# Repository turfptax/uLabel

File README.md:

# uLabel
Machine Learning Label System for regression finger movement models

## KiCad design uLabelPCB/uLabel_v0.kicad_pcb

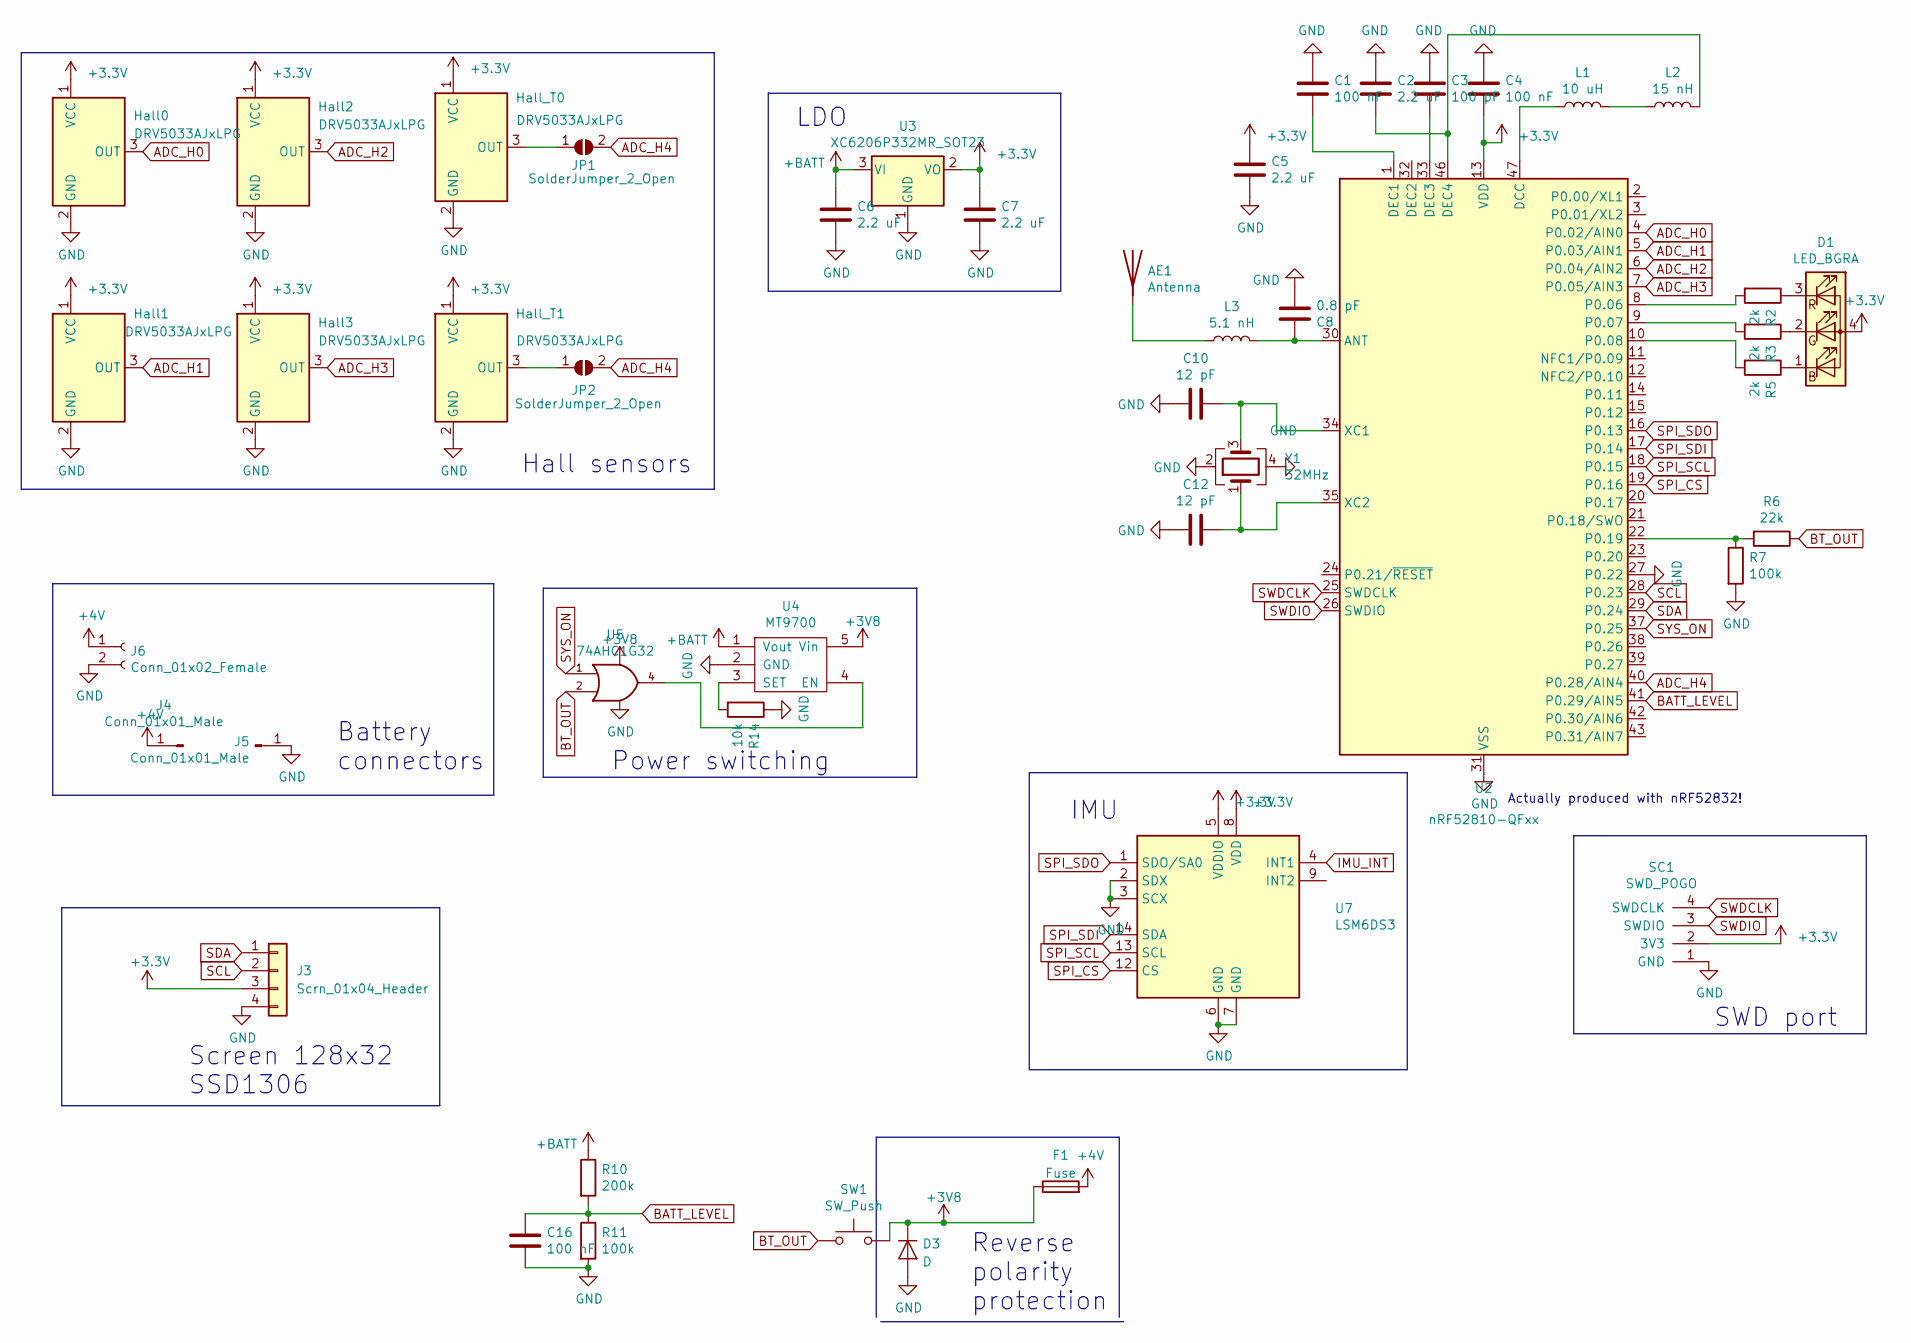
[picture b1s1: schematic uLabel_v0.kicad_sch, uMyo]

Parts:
AE1: Antenna; KH3216-A55; JLCPN C484541
C1, C4, C16: 100 nF; C_0402_1005Metric; JLCPN C1525
C2, C5, C6, C7: 2.2 uF; C_0402_1005Metric; JLCPN C12530
C3: 100 pF; C_0402_1005Metric; JLCPN C1546
C8: 0.8 pF; C_0402_1005Metric; JLCPN C88902
C10, C12: 12 pF; C_0402_1005Metric; JLCPN C1547
D1: LED_BGRA; LED_RGB_0603_a4; JLCPN C282128
D3: D; D_SOD-323; JLCPN C191023
F1: Fuse; Fuse_0603_1608Metric; JLCPN C207011
Hall0, Hall1, Hall2, Hall3: DRV5033AJxLPG; TO-92_Inline
Hall_T0, Hall_T1: DRV5033AJxLPG; TO-92_Inline
J3: Scrn_01x04_Header; PinHeader_1x04_P2.54mm_Vertical
J4, J5: Conn_01x01_Male; conn_16_20
J6: Conn_01x02_Female; JST_PH_S2B-PH-SM4-TB_1x02-1MP_P2.00mm_Horizontal; JLCPN C520130
JP1, JP2: SolderJumper_2_Open; SolderJumper-2_P1.3mm_Open_RoundedPad1.0x1.5mm
L1: 10 uH; L_0603_1608Metric; JLCPN C1035
L2: 15 nH; L_0402_1005Metric; JLCPN C27143
L3: 5.1 nH; L_0402_1005Metric; JLCPN C86066
R2, R3, R5: 2k; R_0402_1005Metric; JLCPN C4109
R6: 22k; R_0402_1005Metric; JLCPN C25768
R7, R11: 100k; R_0402_1005Metric; JLCPN C25741
R10: 200k; R_0402_1005Metric; JLCPN C25764
R14: 10k; R_0402_1005Metric; JLCPN C25744
SC1: SWD_POGO
SW1: SW_Push; SW_SPST_CK_RS282G05A3; JLCPN C2845294
U2: nRF52810-QFxx; QFN-48-1EP_6x6mm_Pitch0.4mm; JLCPN C141828
U3: XC6206P332MR_SOT23; SOT-23; JLCPN C5446
U4: MT9700; SOT-23-5; JLCPN C89855
U5: 74AHC1G32; SOT-23-5; JLCPN C507209
U7: LSM6DS3; LGA-14_3x2.5mm_P0.5mm_LayoutBorder3x4y; JLCPN C967633
Y1: 32MHz; Crystal_SMD_2016-4Pin_2.0x1.6mm; JLCPN C843260

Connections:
+3V3: C4.1, C5.2, C7.2, D1.4 (A), Hall0.1 (VCC), Hall1.1 (VCC), Hall2.1 (VCC), Hall3.1 (VCC), Hall_T0.1 (VCC), Hall_T1.1 (VCC), J3.3, SC1.2 (3V3), U2.13 (VDD), U2.36 (VDD), U2.48 (VDD), U3.2 (VO), U7.5 (VDDIO), U7.8 (VDD)
+3V8: D3.1 (K), F1.1, SW1.2, U4.5 (Vin), U5.5 (VCC)
+4V: F1.2, J4.1, J6.1
+BATT: C6.2, R10.1, U3.3 (VI), U4.1 (Vout)
ADC_H0: Hall0.3 (OUT), U2.4 (P0.02/AIN0)
ADC_H1: Hall1.3 (OUT), U2.5 (P0.03/AIN1)
ADC_H2: Hall2.3 (OUT), U2.6 (P0.04/AIN2)
ADC_H3: Hall3.3 (OUT), U2.7 (P0.05/AIN3)
ADC_H4: JP1.2 (B), JP2.2 (B), U2.40 (P0.28/AIN4)
BATT_LEVEL: C16.2, R10.2, R11.1, U2.41 (P0.29/AIN5)
BT_OUT: R6.1, SW1.1, U5.2
GND: C1.2, C2.2, C3.2, C4.2, C5.1, C6.1, C7.1, C8.2, C10.1, C12.1, C16.1, D3.2 (A), Hall0.2 (GND), Hall1.2 (GND), Hall2.2 (GND), Hall3.2 (GND), Hall_T0.2 (GND), Hall_T1.2 (GND), J3.4, J5.1, J6.2, R7.2, R11.2, R14.1, SC1.1 (GND), U2.27 (P0.22), U2.31 (VSS), U2.45 (VSS), U2.49 (VSS), U3.1 (GND), U4.2 (GND), U5.3 (GND), U7.2 (SDX), U7.3 (SCX), U7.6 (GND), U7.7 (GND), Y1.2, Y1.4
IMU_INT: U7.4 (INT1)
unnamed: AE1.1 (A), L3.1
unnamed: D1.1 (BK), R5.1
unnamed: D1.2 (GK), R3.1
unnamed: D1.3 (RK), R2.1
unnamed: Hall_T0.3 (OUT), JP1.1 (A)
unnamed: Hall_T1.3 (OUT), JP2.1 (A)
unnamed: L1.2, L2.1
unnamed: C8.1, L3.2, U2.30 (ANT)
unnamed: L1.1, U2.47 (DCC)
unnamed: C1.1, U2.1 (DEC1)
unnamed: C3.1, U2.33 (DEC3)
unnamed: C2.1, L2.2, U2.46 (DEC4)
unnamed: R2.2, U2.8 (P0.06)
unnamed: R3.2, U2.9 (P0.07)
unnamed: R5.2, U2.10 (P0.08)
unnamed: R6.2, R7.1, U2.22 (P0.19)
unnamed: C10.2, U2.34 (XC1), Y1.3
unnamed: C12.2, U2.35 (XC2), Y1.1
unnamed: U4.4 (EN), U5.4
unnamed: R14.2, U4.3 (SET)
SCL: J3.2, U2.28 (P0.23)
SDA: J3.1, U2.29 (P0.24)
SPI_CS: U2.19 (P0.16), U7.12 (CS)
SPI_SCL: U2.18 (P0.15), U7.13 (SCL)
SPI_SDI: U2.17 (P0.14), U7.14 (SDA)
SPI_SDO: U2.16 (P0.13), U7.1 (SDO/SA0)
SWDCLK: SC1.4 (SWDCLK), U2.25 (SWDCLK)
SWDIO: SC1.3 (SWDIO), U2.26 (SWDIO)
SYS_ON: U2.37 (P0.25), U5.1

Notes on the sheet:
SWD port
Power switching
Battery connectors
IMU
Reverse polarity protection
LDO
Hall sensors
Actually produced with nRF52832!
Screen 128x32 SSD1306

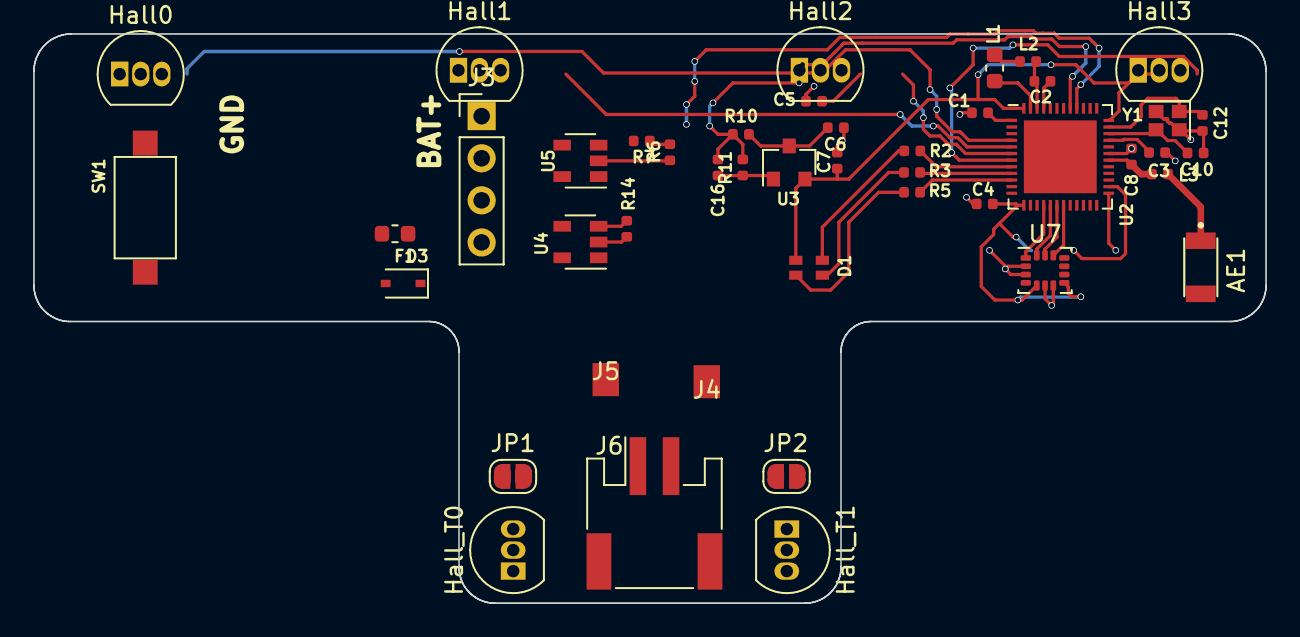
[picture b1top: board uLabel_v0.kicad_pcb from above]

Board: 2 copper layers, 74.4 x 34.4 mm, 46 parts (1 on the bottom side), 41 nets.

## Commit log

2023-11-23 Main Files Upload
2023-11-23 Main Firmware Files
2024-10-22 Add STL Files
